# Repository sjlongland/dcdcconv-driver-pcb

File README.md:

[Find this project on codeberg](https://codeberg.org/sjlongland/dcdcconv-driver-pcb)

As a result of Github's decision to force AI-generated issues with no opt-out,
I am migrating personal projects of mine to Codeberg.  The project at Github
will be archived.

----

# PWM MOSFET driver board

This is a LVDS-compatible MOSFET driver board for use with the [DC-DC converter
board](https://codeberg.org/sjlongland/dcdcconv-controller-pcb).  It can drive
two N-Channel MOSFETs, either mounting the leads through the supplied
connection points `J3` and `J4` (suitable for TO-220 size MOSFETs) or via short
connection cables.  Due to parasitic inductance, it is best these be kept as
short as practical.

## Parts list

* U1: TI DS90C402 dual-channel LVDS receiver
* U2: TI UCC27212A-Q1 high/low side N-MOSFET driver
* U3: 74AHC04 (SOIC-14) hex inverting buffer (U1 when not connected to a LVDS
  source will drive both its outputs high, this inverts this to ensure both MOSFETs
  remain off in this condition.)
* C2: ≥100µF ≥10V electrolytic capacitor 6.3mm SMD (Bulk 5V rail decoupling)
* C1, C10: 100nF ≥10V ceramic capacitor 0805 SMD (local decoupling for U1, U3)
* C3: ≥100µF ≥20V electrolytic capacitor 6.3mm SMD (Bulk 12V rail decoupling)
* C4: 100nF ≥20V ceramic capacitor 0805 SMD (local decoupling for U2)
* C5: Bootstrap electrolyic capacitor for U2, refer to data sheet.  6.3mm SMD.
* J1: 6-pin 2.54mm "KK" connector (LVDS input and 5V rail)
* J2: 2-pin 2.54mm "KK" connector (12V rail)
* J3, J4: 3-pin 2.54mm "KK" connector or TO-220 size MOSFETs with heatsinks.
* (**FIT ONE ONLY**) C6, C7, C8, C9: ~100pF ≥20V ceramic capacitor 0805 (0V AC
  de-coupling to chassis.  Choose the one that best suits your mounting
  requirements.)

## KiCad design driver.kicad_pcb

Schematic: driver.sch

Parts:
C1, C4, C10: 100n; C_0805_2012Metric_Pad1.15x1.40mm_HandSolder
C2, C3: 100u; CP_Elec_6.3x9.9
C5: CP; CP_Elec_6.3x9.9
C6, C7, C8, C9: 100p; C_0805_2012Metric_Pad1.15x1.40mm_HandSolder
J1: CTRL; Molex_KK-254_AE-6410-06A_1x06_P2.54mm_Vertical
J2: 12V_IN; Molex_KK-254_AE-6410-02A_1x02_P2.54mm_Vertical
J3: HIGH_MOSFET; PinHeader_1x03_P2.54mm_Vertical
J4: LOW_MOSFET; PinHeader_1x03_P2.54mm_Vertical
MH1, MH2, MH3, MH4: MountingHole_Pad; MountingHole_3mm_Pad_Via
R1, R2, R3, R4, R5, R6, R7, R8: 2k2; R_0805_2012Metric_Pad1.15x1.40mm_HandSolder
R9, R10: 100R; R_0805_2012Metric_Pad1.15x1.40mm_HandSolder
U1: DS90C402; SOIC-8_3.9x4.9mm_P1.27mm
U2: UCC27212A-Q1; TI_SO-PowerPAD-8_ThermalVias
U3: 74AHC04; SOIC-14_3.9x8.7mm_P1.27mm

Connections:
+5V: C1.1, C2.1, C10.1, J1.1, R1.1, R3.1, R5.1, R7.1, U1.1, U3.11, U3.13, U3.14 (VCC)
+12V: C3.1, C4.1, J2.1, U2.1
/HI+: J1.3, R1.2, R2.1, R9.2, U1.3
/HI-: J1.4, R3.2, R4.1, R9.1, U1.4
/HI_GATE: J3.1, U2.3
/HI_SRC: C5.2, J3.3, U2.4
/LO+: J1.5, R5.2, R6.1, R10.2, U1.7
/LO-: J1.6, R7.2, R8.1, R10.1, U1.8
/LO_GATE: J4.1, U2.8
/~HI~: U1.2, U3.1
/~LO~: U1.6, U3.3
GND: C1.2, C2.2, C3.2, C4.2, C6.2, C7.2, C8.2, C9.2, C10.2, J1.2, J2.2, J4.3, R2.2, R4.2, R6.2, R8.2, U1.5, U2.7, U2.9, U3.5, U3.7 (GND), U3.9
unnamed: C5.1, U2.2
unnamed: C6.1, MH1.1
unnamed: C7.1, MH2.1
unnamed: C8.1, MH3.1
unnamed: C9.1, MH4.1
unnamed: U2.5, U3.2
unnamed: U2.6, U3.4

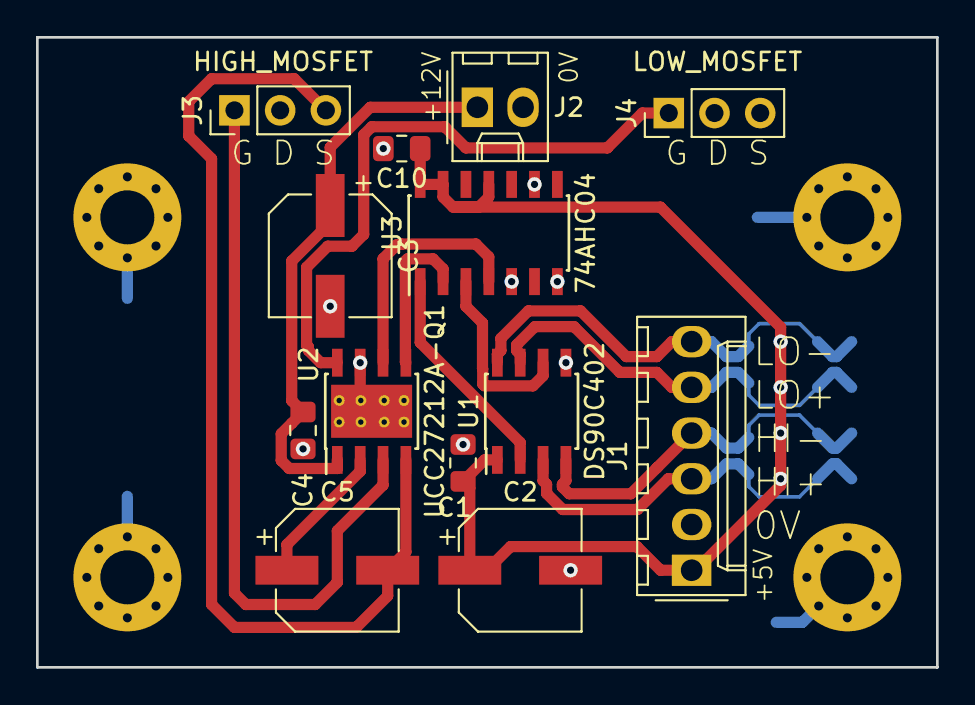
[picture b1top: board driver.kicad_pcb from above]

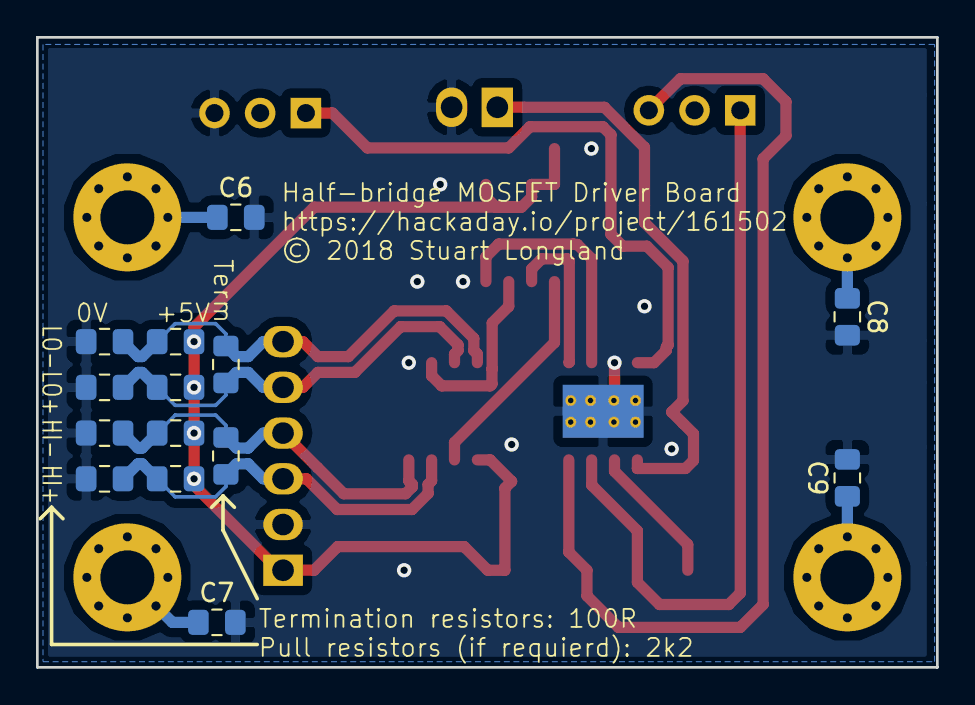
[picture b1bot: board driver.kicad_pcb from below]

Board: 2 copper layers, 50.0 x 35.0 mm, 31 parts (14 on the bottom side), 19 nets.

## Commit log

2018-10-07 Initial check-in
2018-10-22 pcb: Finalise for prototype run.
2018-10-22 gerber: Add CAM production files.
2025-05-30 README.md: update regarding move of project

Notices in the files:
driver.kicad_pcb:
© 2018 Stuart Longland
